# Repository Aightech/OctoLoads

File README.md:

# OctoLoads: 8-Channel Load Cell Measurement PCB

OctoLoads is an 8-channel load cell measurement Printed Circuit Board (PCB) designed for projects that require simultaneous readings from multiple load cells. With 8 HX711 modules on a single board, it offers a practical and efficient solution for managing and synchronizing measurements across several load cells.

## Visualisation
Top             |  Bottom 
:-------------------------:|:-------------------------:
 |  

## Features

    8 HX711 modules for measuring up to 8 load cells simultaneously
    Shared clock bus for perfectly synchronized measurements
    Selectable sampling rate: 10Hz or 80Hz
    Compatible with various load cells
    Optimized PCB layout for signal integrity, power distribution, and thermal management

## Applications

    Industrial weighing systems
    Multi-axis force/torque measurements
    Robotics and automation
    Agricultural and food processing equipment
    Fitness and sports equipment

## Getting Started

    Hardware Setup: Connect your load cells to the octoLoads board following the appropriate wiring diagram provided in the documentation.

    Sampling Rate Selection: Choose between the two available sampling rates (10Hz or 80Hz) by setting the jumper on the board as described in the documentation.

    Microcontroller Integration: Connect the octoLoads board to your microcontroller or processing unit, and utilize the provided library or API for seamless integration.

    Software Setup: Import the provided octoLoads library into your project, and follow the example code in the documentation to start taking measurements from your load cells.

## Documentation

Detailed documentation, including schematics, layout files, and instructions for use, is available in the docs folder.

## Support

For any questions or issues, please raise an issue'

## License
This project is licensed under the MIT License - see the LICENSE file for details.

## Code
### Building source code

To build the project run:
```bash
cd octoLoads
mkdir build && cd build
cmake .. && make
```

### Demonstration app

When the project have been built, you can run:
```bash
./octoLoads -h
```
to get the demonstration app usage.

### Example
Open the  file to get an example how to use the lib.

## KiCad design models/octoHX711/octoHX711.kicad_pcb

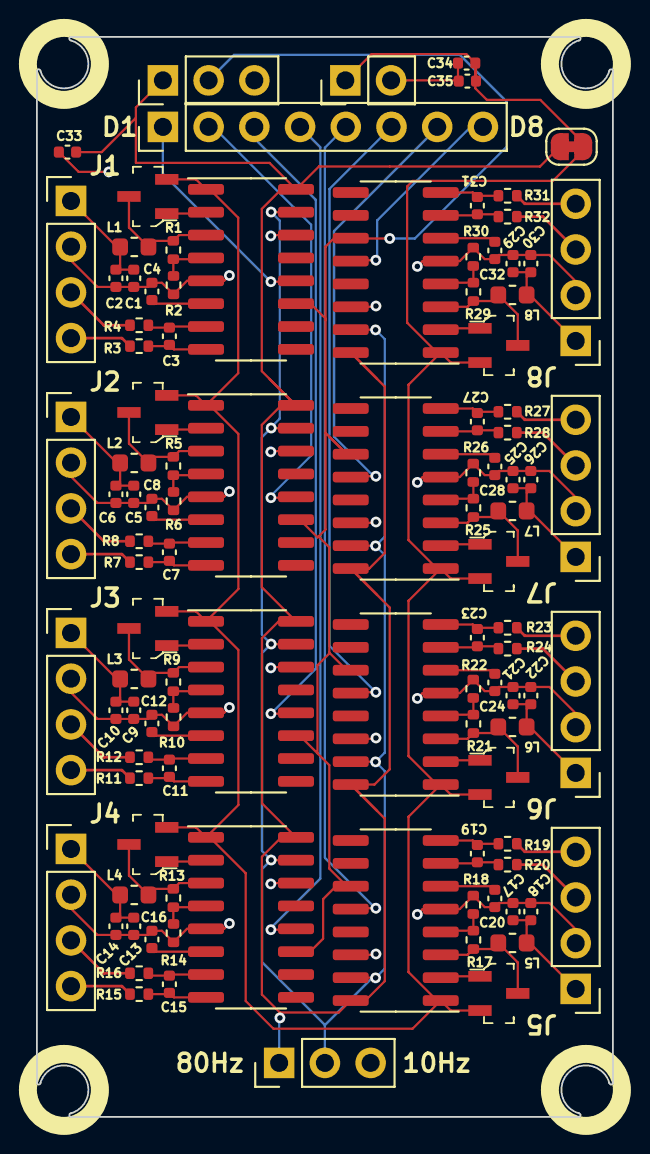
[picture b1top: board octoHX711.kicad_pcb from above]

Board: 4 copper layers, 32.0 x 60.0 mm, 104 parts (0 on the bottom side), 85 nets.

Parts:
C1, C3, C4, C5, C7, C8, C9, C11, C12, C13, C15, C16, C17, C19, C20, C21, C23, C24, C25, C27, C28, C29, C31, C32, C33, C34: 100nF; C_0402_1005Metric
C2, C6, C10, C14, C18, C22, C26, C30, C35: 10uF; C_0402_1005Metric
J1, J2, J3, J4, J5, J6, J7, J8: Conn_01x04_Male; PinHeader_1x04_P2.54mm_Vertical
J9: Conn_01x08_Male; PinHeader_1x08_P2.54mm_Vertical
J10, J12: Conn_01x03_Male; PinHeader_1x03_P2.54mm_Vertical
J11: Conn_01x02_Male; PinHeader_1x02_P2.54mm_Vertical
JP1: SolderJumper_2_Bridged; SolderJumper-2_P1.3mm_Bridged_RoundedPad1.0x1.5mm
L1, L2, L3, L4, L5, L6, L7, L8: 3.3uH; L_0603_1608Metric
Q1, Q2, Q3, Q4, Q5, Q6, Q7, Q8: MMBT4403LT1G; SOT-23-3
R1, R5, R9, R13, R17, R21, R25, R29: 20k; R_0402_1005Metric
R2, R6, R10, R14, R18, R22, R26, R30: 8.2k; R_0402_1005Metric
R3, R4, R7, R8, R11, R12, R15, R16, R19, R20, R23, R24, R27, R28, R31, R32: 100; R_0402_1005Metric
U1, U2, U3, U4, U5, U6, U7, U8: HX711; SOP-16_3.9x9.9mm_P1.27mm

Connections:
/HX711_unit1/Sdat: J9.1, U1.12 (DOUT)
/HX711_unit1/a+: J1.4, R3.1
/HX711_unit1/a+in: C3.1, R3.2, U1.8 (INA+)
/HX711_unit1/a-: J1.3, R4.1
/HX711_unit1/a-in: C3.2, R4.2, U1.7 (INA-)
/HX711_unit1/avdd: L1.2, Q1.3 (C), R1.1, U1.3 (AVDD)
/HX711_unit1/base: Q1.1 (B), U1.2 (BASE)
/HX711_unit1/e+: C1.1, C2.1, J1.1, L1.1
/HX711_unit1/vbg: C4.1, U1.6 (VBG)
/HX711_unit1/vfb: R1.2, R2.1, U1.4 (VFB)
/HX711_unit2/Sdat: J9.2, U2.12 (DOUT)
/HX711_unit2/a+: J2.4, R7.1
/HX711_unit2/a+in: C7.1, R7.2, U2.8 (INA+)
/HX711_unit2/a-: J2.3, R8.1
/HX711_unit2/a-in: C7.2, R8.2, U2.7 (INA-)
/HX711_unit2/avdd: L2.2, Q2.3 (C), R5.1, U2.3 (AVDD)
/HX711_unit2/base: Q2.1 (B), U2.2 (BASE)
/HX711_unit2/e+: C5.1, C6.1, J2.1, L2.1
/HX711_unit2/vbg: C8.1, U2.6 (VBG)
/HX711_unit2/vfb: R5.2, R6.1, U2.4 (VFB)
/HX711_unit3/Sdat: J9.3, U3.12 (DOUT)
/HX711_unit3/a+: J3.4, R11.1
/HX711_unit3/a+in: C11.1, R11.2, U3.8 (INA+)
/HX711_unit3/a-: J3.3, R12.1
/HX711_unit3/a-in: C11.2, R12.2, U3.7 (INA-)
/HX711_unit3/avdd: L3.2, Q3.3 (C), R9.1, U3.3 (AVDD)
/HX711_unit3/base: Q3.1 (B), U3.2 (BASE)
/HX711_unit3/e+: C9.1, C10.1, J3.1, L3.1
/HX711_unit3/vbg: C12.1, U3.6 (VBG)
/HX711_unit3/vfb: R9.2, R10.1, U3.4 (VFB)
/HX711_unit4/Sdat: J9.4, U4.12 (DOUT)
/HX711_unit4/a+: J4.4, R15.1
/HX711_unit4/a+in: C15.1, R15.2, U4.8 (INA+)
/HX711_unit4/a-: J4.3, R16.1
/HX711_unit4/a-in: C15.2, R16.2, U4.7 (INA-)
/HX711_unit4/avdd: L4.2, Q4.3 (C), R13.1, U4.3 (AVDD)
/HX711_unit4/base: Q4.1 (B), U4.2 (BASE)
/HX711_unit4/e+: C13.1, C14.1, J4.1, L4.1
/HX711_unit4/vbg: C16.1, U4.6 (VBG)
/HX711_unit4/vfb: R13.2, R14.1, U4.4 (VFB)
/HX711_unit5/Sdat: J9.5, U5.12 (DOUT)
/HX711_unit5/a+: J5.4, R19.1
/HX711_unit5/a+in: C19.1, R19.2, U5.8 (INA+)
/HX711_unit5/a-: J5.3, R20.1
/HX711_unit5/a-in: C19.2, R20.2, U5.7 (INA-)
/HX711_unit5/avdd: L5.2, Q5.3 (C), R17.1, U5.3 (AVDD)
/HX711_unit5/base: Q5.1 (B), U5.2 (BASE)
/HX711_unit5/e+: C17.1, C18.1, J5.1, L5.1
/HX711_unit5/vbg: C20.1, U5.6 (VBG)
/HX711_unit5/vfb: R17.2, R18.1, U5.4 (VFB)
/HX711_unit6/Sdat: J9.7, U7.12 (DOUT)
/HX711_unit6/a+: J7.4, R27.1
/HX711_unit6/a+in: C27.1, R27.2, U7.8 (INA+)
/HX711_unit6/a-: J7.3, R28.1
/HX711_unit6/a-in: C27.2, R28.2, U7.7 (INA-)
/HX711_unit6/avdd: L7.2, Q7.3 (C), R25.1, U7.3 (AVDD)
/HX711_unit6/base: Q7.1 (B), U7.2 (BASE)
/HX711_unit6/e+: C25.1, C26.1, J7.1, L7.1
/HX711_unit6/vbg: C28.1, U7.6 (VBG)
/HX711_unit6/vfb: R25.2, R26.1, U7.4 (VFB)
/HX711_unit7/Sdat: J9.8, U8.12 (DOUT)
/HX711_unit7/a+: J8.4, R31.1
/HX711_unit7/a+in: C31.1, R31.2, U8.8 (INA+)
/HX711_unit7/a-: J8.3, R32.1
/HX711_unit7/a-in: C31.2, R32.2, U8.7 (INA-)
/HX711_unit7/avdd: L8.2, Q8.3 (C), R29.1, U8.3 (AVDD)
/HX711_unit7/base: Q8.1 (B), U8.2 (BASE)
/HX711_unit7/e+: C29.1, C30.1, J8.1, L8.1
/HX711_unit7/vbg: C32.1, U8.6 (VBG)
/HX711_unit7/vfb: R29.2, R30.1, U8.4 (VFB)
/HX711_unit8/Sdat: J9.6, U6.12 (DOUT)
/HX711_unit8/a+: J6.4, R23.1
/HX711_unit8/a+in: C23.1, R23.2, U6.8 (INA+)
/HX711_unit8/a-: J6.3, R24.1
/HX711_unit8/a-in: C23.2, R24.2, U6.7 (INA-)
/HX711_unit8/avdd: L6.2, Q6.3 (C), R21.1, U6.3 (AVDD)
/HX711_unit8/base: Q6.1 (B), U6.2 (BASE)
/HX711_unit8/e+: C21.1, C22.1, J6.1, L6.1
/HX711_unit8/vbg: C24.1, U6.6 (VBG)
/HX711_unit8/vfb: R21.2, R22.1, U6.4 (VFB)
GND: C1.2, C2.2, C4.2, C5.2, C6.2, C8.2, C9.2, C10.2, C12.2, C13.2, C14.2, C16.2, C17.2, C18.2, C20.2, C21.2, C22.2, C24.2, C25.2, C26.2, C28.2, C29.2, C30.2, C32.2, C33.1, C34.1, C35.1, J1.2, J2.2, J3.2, J4.2, J5.2, J6.2, J7.2, J8.2, J10.3, J11.2, J12.3, R2.2, R6.2, R10.2, R14.2, R18.2, R22.2, R26.2, R30.2, U1.5 (AGND), U1.14 (XI), U2.5 (AGND), U2.14 (XI), U3.5 (AGND), U3.14 (XI), U4.5 (AGND), U4.14 (XI), U5.5 (AGND), U5.14 (XI), U6.5 (AGND), U6.14 (XI), U7.5 (AGND), U7.14 (XI), U8.5 (AGND), U8.14 (XI)
Sclk: J10.2, U1.11 (PD_SCK), U2.11 (PD_SCK), U3.11 (PD_SCK), U4.11 (PD_SCK), U5.11 (PD_SCK), U6.11 (PD_SCK), U7.11 (PD_SCK), U8.11 (PD_SCK)
VCC: C34.2, C35.2, J11.1, JP1.2 (B), Q1.2 (E), Q2.2 (E), Q3.2 (E), Q4.2 (E), Q5.2 (E), Q6.2 (E), Q7.2 (E), Q8.2 (E), U1.1 (VSUP), U2.1 (VSUP), U3.1 (VSUP), U4.1 (VSUP), U5.1 (VSUP), U6.1 (VSUP), U7.1 (VSUP), U8.1 (VSUP)
VDD: C33.2, J10.1, J12.1, JP1.1 (A), U1.16 (DVDD), U2.16 (DVDD), U3.16 (DVDD), U4.16 (DVDD), U5.16 (DVDD), U6.16 (DVDD), U7.16 (DVDD), U8.16 (DVDD)
rate: J12.2, U1.15 (RATE), U2.15 (RATE), U3.15 (RATE), U4.15 (RATE), U5.15 (RATE), U6.15 (RATE), U7.15 (RATE), U8.15 (RATE)

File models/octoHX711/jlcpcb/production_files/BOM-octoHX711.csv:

Comment,Designator,Footprint,LCSC
3.3uH,"L1,L2,L3,L4,L5,L6,L7,L8",L_0603_1608Metric,C139209
100nF,"C1,C11,C12,C13,C15,C16,C17,C19,C20,C21,C23,C24,C25,C27,C28,C29,C3,C31,C32,C33,C34,C4,C5,C7,C8,C9",C_0402_1005Metric,C1525
10uF,"C10,C14,C18,C2,C22,C26,C30,C35,C6",C_0402_1005Metric,C15525
100,"R11,R12,R15,R16,R19,R20,R23,R24,R27,R28,R3,R31,R32,R4,R7,R8",R_0402_1005Metric,C25076
20k,"R1,R13,R17,R21,R25,R29,R5,R9",R_0402_1005Metric,C25765
8.2k,"R10,R14,R18,R2,R22,R26,R30,R6",R_0402_1005Metric,C25924
HX711,"U1,U2,U3,U4,U5,U6,U7,U8",SOP-16_3.9x9.9mm_P1.27mm,C43656
MMBT4403LT1G,"Q1,Q2,Q3,Q4,Q5,Q6,Q7,Q8",SOT-23-3,C78864

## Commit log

2023-05-07 added img to readme
2023-07-04 fixed silkscreen and added arduino lib
